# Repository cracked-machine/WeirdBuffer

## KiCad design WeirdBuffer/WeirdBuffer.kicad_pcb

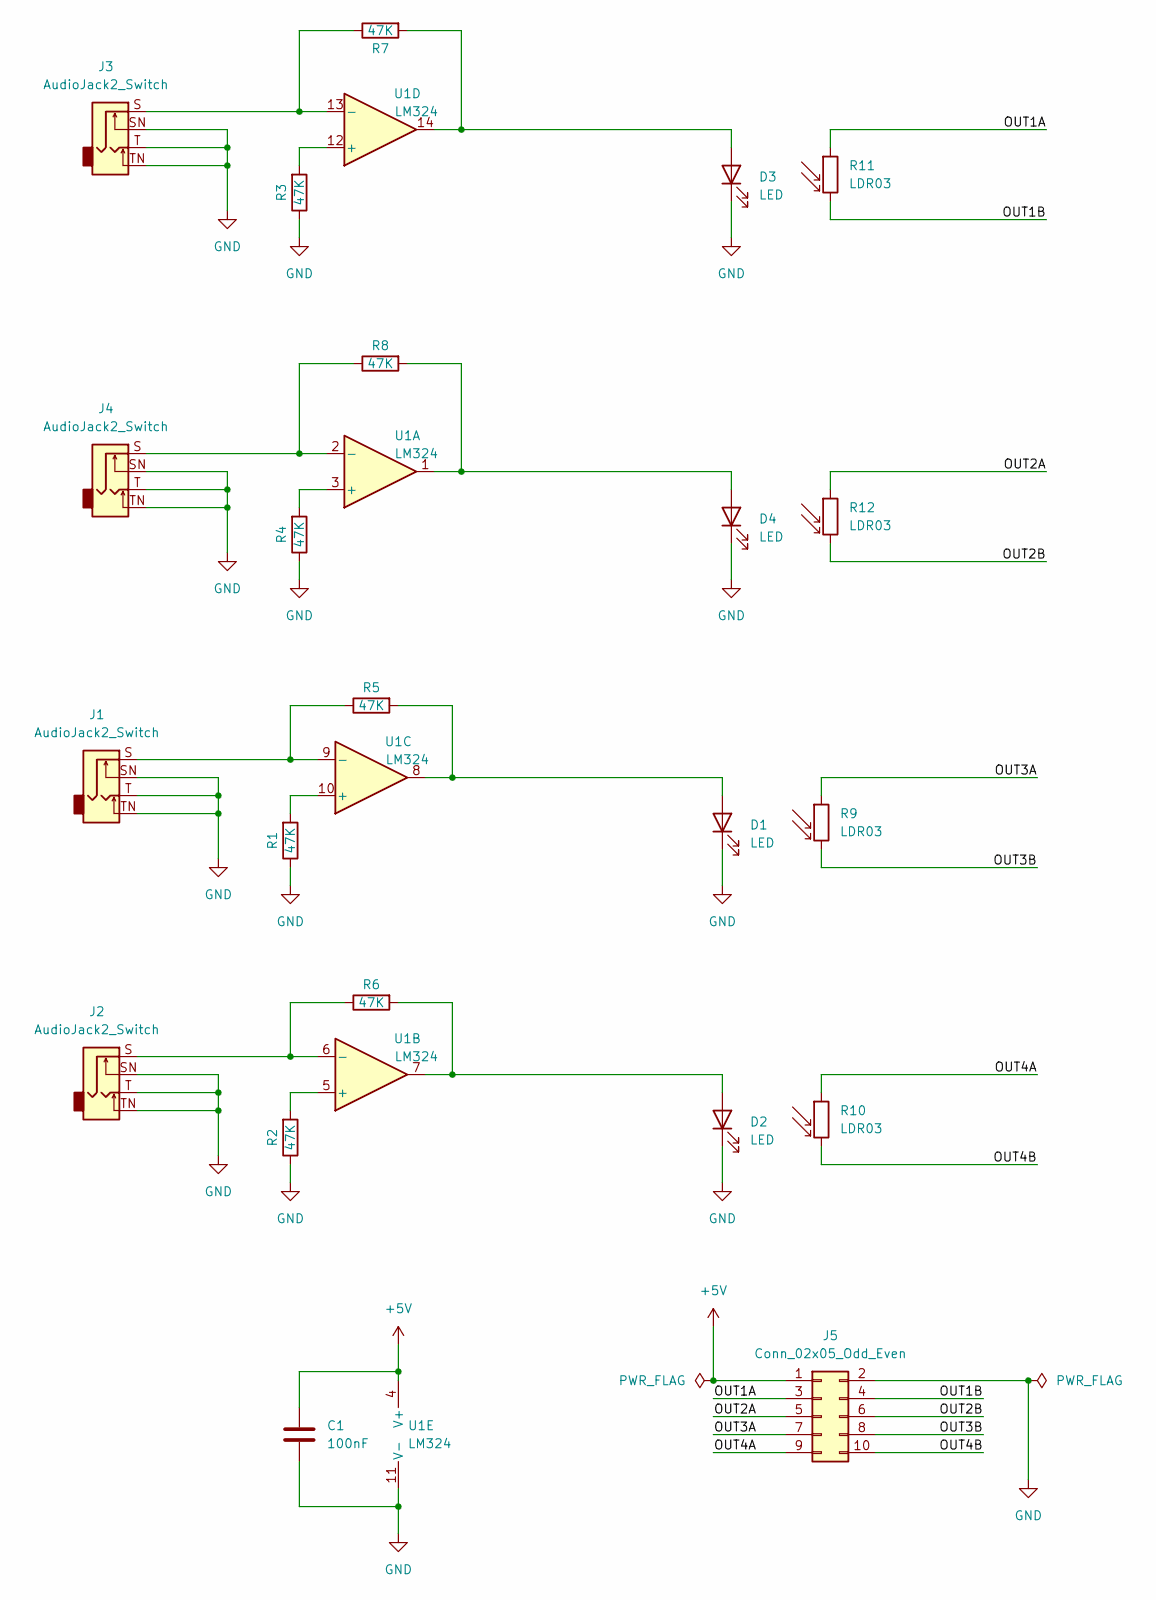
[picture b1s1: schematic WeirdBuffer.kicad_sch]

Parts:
C1: 100nF; C_0805_2012Metric
D1, D2, D3, D4: LED; LED_D5.0mm
J1, J2, J3, J4: AudioJack2_Switch; Jack_6.35mm_Neutrik_NMJ4HFD2_Horizontal
J5: Conn_02x05_Odd_Even; IDC-Header_2x05_P2.54mm_Horizontal
R1, R2, R3, R4, R5, R6, R7, R8: 47K; R_0805_2012Metric_Pad1.20x1.40mm_HandSolder
R9, R10, R11, R12: LDR03; R_LDR_10x8.5mm_P7.6mm_Vertical
U1: LM324; DIP-14_W7.62mm_LongPads

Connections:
+5V: C1.1, J5.1, U1.4 (V+)
/OUT1A: J5.3, R11.1
/OUT1B: J5.4, R11.2
/OUT2A: J5.5, R12.1
/OUT2B: J5.6, R12.2
/OUT3A: J5.7, R9.1
/OUT3B: J5.8, R9.2
/OUT4A: J5.9, R10.1
/OUT4B: J5.10, R10.2
GND: C1.2, D1.1 (K), D2.1 (K), D3.1 (K), D4.1 (K), J1.SN, J1.T, J1.TN, J2.SN, J2.T, J2.TN, J3.SN, J3.T, J3.TN, J4.SN, J4.T, J4.TN, J5.2, R1.1, R2.1, R3.1, R4.1, U1.11 (V-)
unnamed: D1.2 (A), R5.2, U1.8
unnamed: D2.2 (A), R6.2, U1.7
unnamed: D3.2 (A), R7.2, U1.14
unnamed: D4.2 (A), R8.2, U1.1
unnamed: R1.2, U1.10 (+)
unnamed: R2.2, U1.5 (+)
unnamed: R3.2, U1.12 (+)
unnamed: R4.2, U1.3 (+)
unnamed: J1.S, R5.1, U1.9 (-)
unnamed: J2.S, R6.1, U1.6 (-)
unnamed: J3.S, R7.1, U1.13 (-)
unnamed: J4.S, R8.1, U1.2 (-)

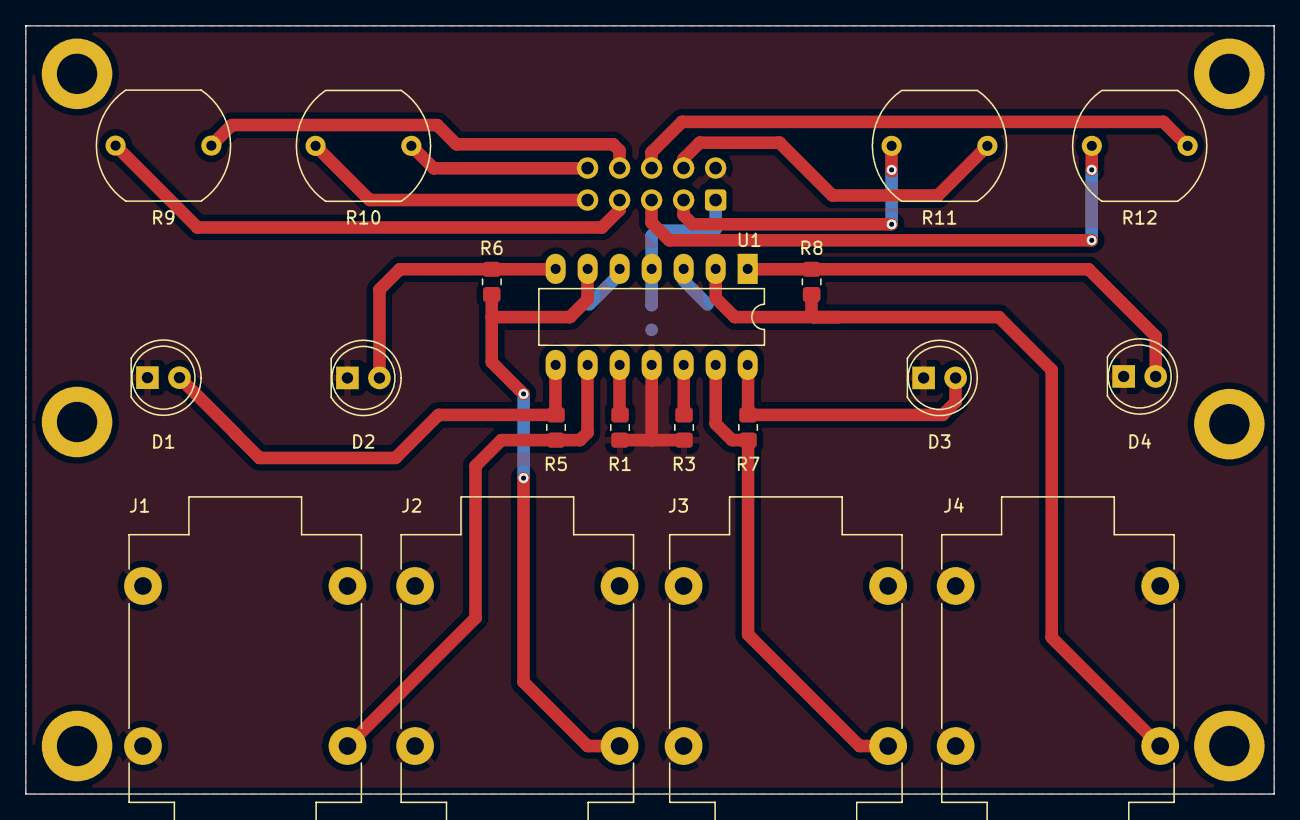
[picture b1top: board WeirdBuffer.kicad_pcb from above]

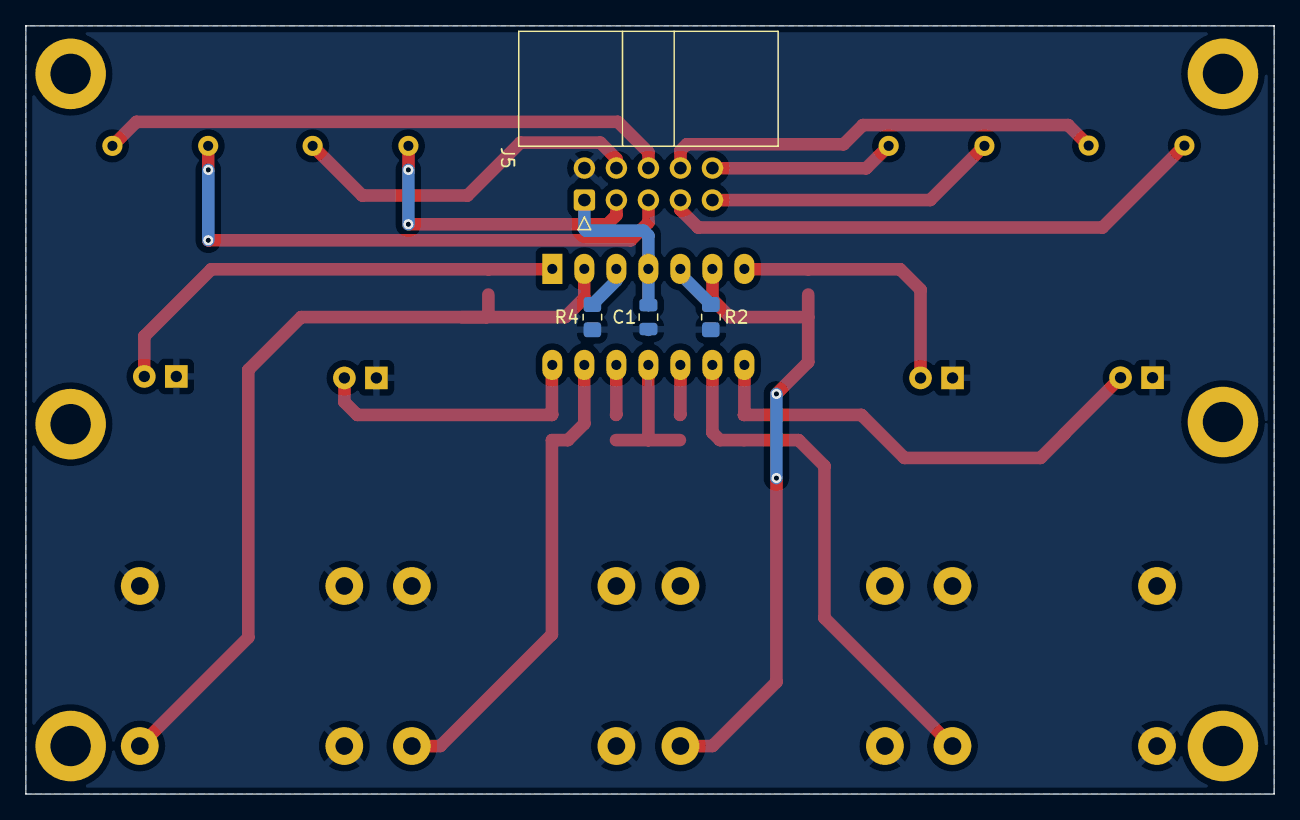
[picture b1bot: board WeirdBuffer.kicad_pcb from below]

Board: 2 copper layers, 99.1 x 61.0 mm, 23 parts (4 on the bottom side), 22 nets.

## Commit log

2022-06-05 first draft
2022-06-06 second draft
2022-06-06 add schematic pdf
